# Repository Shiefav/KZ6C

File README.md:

# KZ6C — six-button CH552 USB macropad (prototype B02.1)

A 64 × 64 mm two-layer PCB with three MX-style switches and three 6 × 6 mm tactile switches, USB-C, CH552G and seven individually addressable RGB LEDs. This is an experimental design: it has not yet been validated on a physical prototype and is not a production-ready release.

- `hardware/`: editable KiCad 10 schematic, PCB, project and project-local libraries.
- `firmware/`: CH552 firmware source, vendored dependencies, attribution and firmware license. Requires SDCC; run `make all` inside that directory to build. No flashing is performed by this command.
- `case/`: preliminary sandwich-case OpenSCAD, DXF outlines and an approximate assembly generator. Switch dimensions, fasteners, LED illumination and actual USB clearance require physical fit checks.

## Prototype checks

Check the tactile switch footprint, pad dimensions, height and paired contacts against actual purchased parts. Check component orientation including the SK6812-EC20 LEDs, and the BOM/CPL in the assembly provider's viewer. Measure the current in full brightness and USB suspend, inrush when the LEDs switch on, USB startup and wake. Test key combinations, flashing recovery and fit of switches, case and USB cable on real hardware.

The development firmware currently reports FEED:4B16 as a temporary test identity. This is not a permanent assigned identifier; obtain an appropriate VID/PID before product release. A successful KiCad DRC/ERC does not prove electrical, USB or mechanical compliance.

## Attribution and licensing

The firmware is based on PadKit and the CH552 USB/NeoPixel stack by Stefan Wagner. Attribution, modifications and the CC BY-SA 3.0 firmware license are in `firmware/ATTRIBUTION.md` and `firmware/LICENSE`. Original hardware and case are CC BY-SA 4.0. The adapted KiCad USB-C footprint carries the KiCad library exception. See the root LICENSE and hardware/ATTRIBUTION.md. Firmware is CC BY-SA 3.0; retain its upstream notices.

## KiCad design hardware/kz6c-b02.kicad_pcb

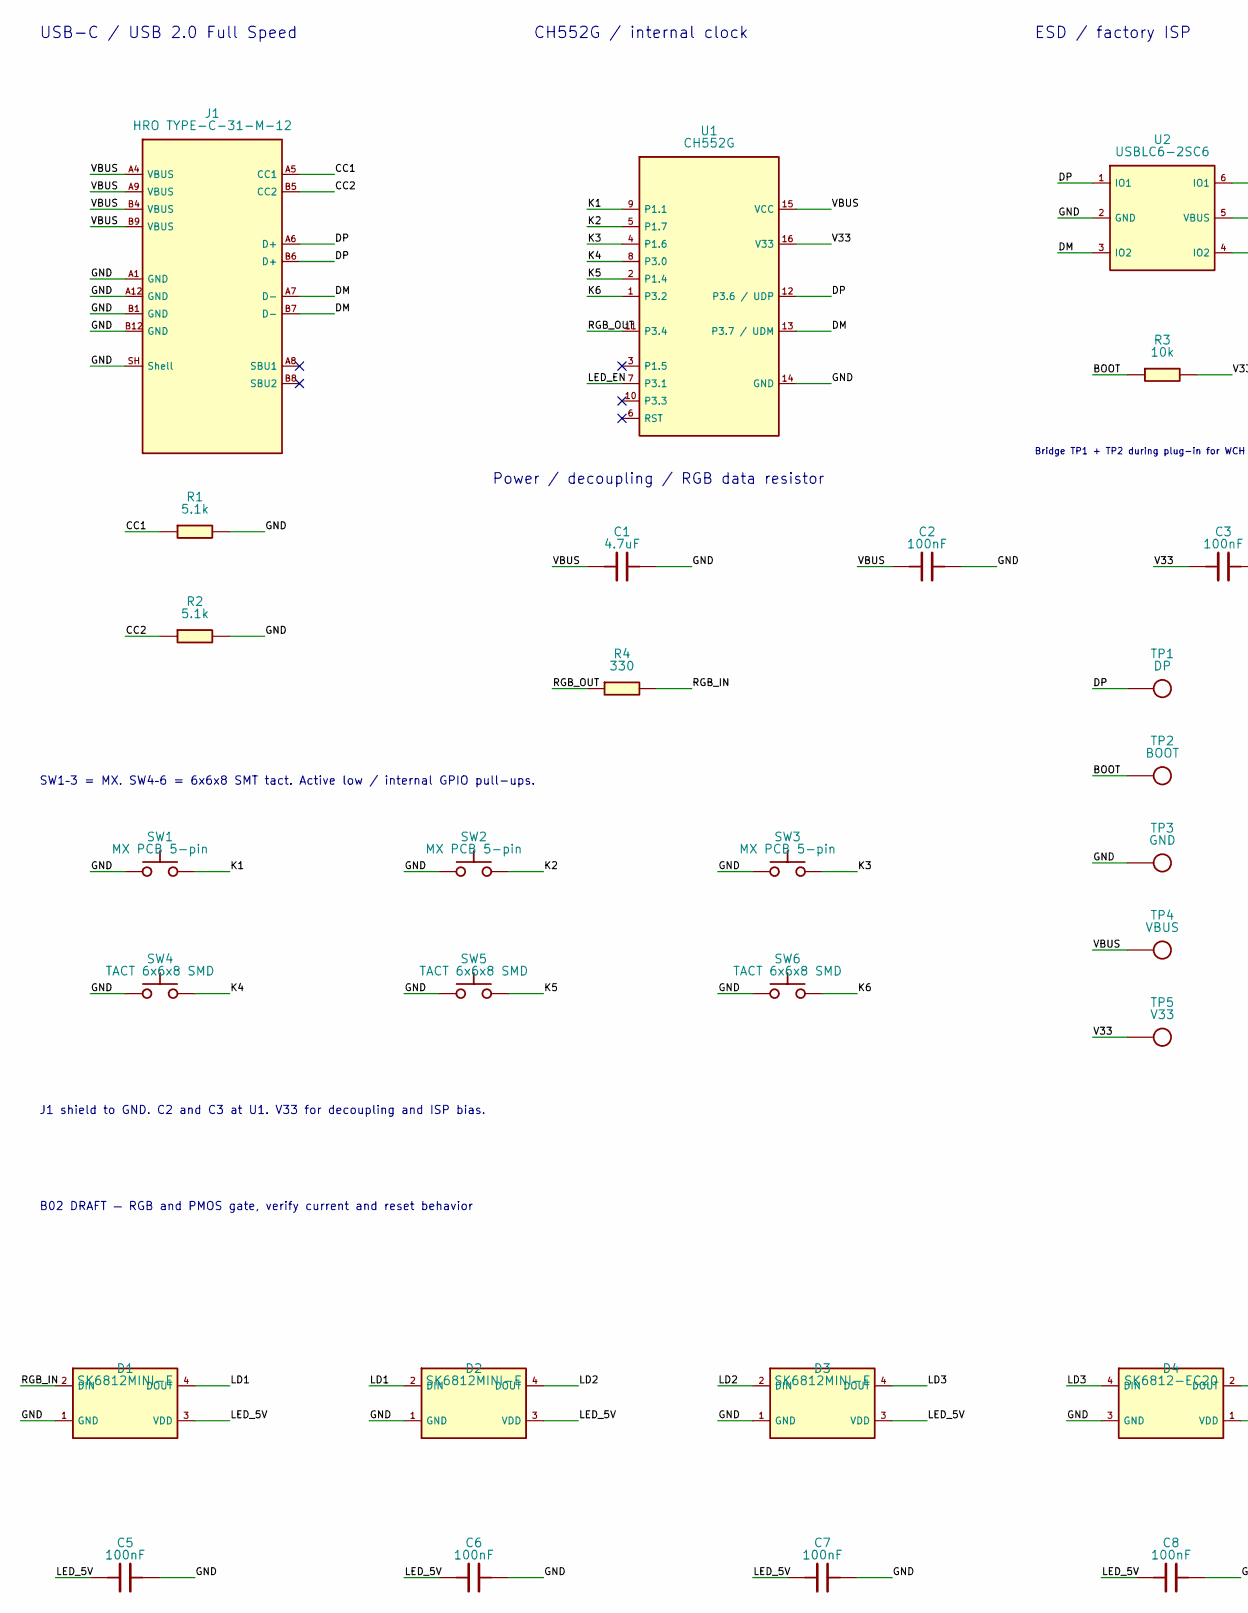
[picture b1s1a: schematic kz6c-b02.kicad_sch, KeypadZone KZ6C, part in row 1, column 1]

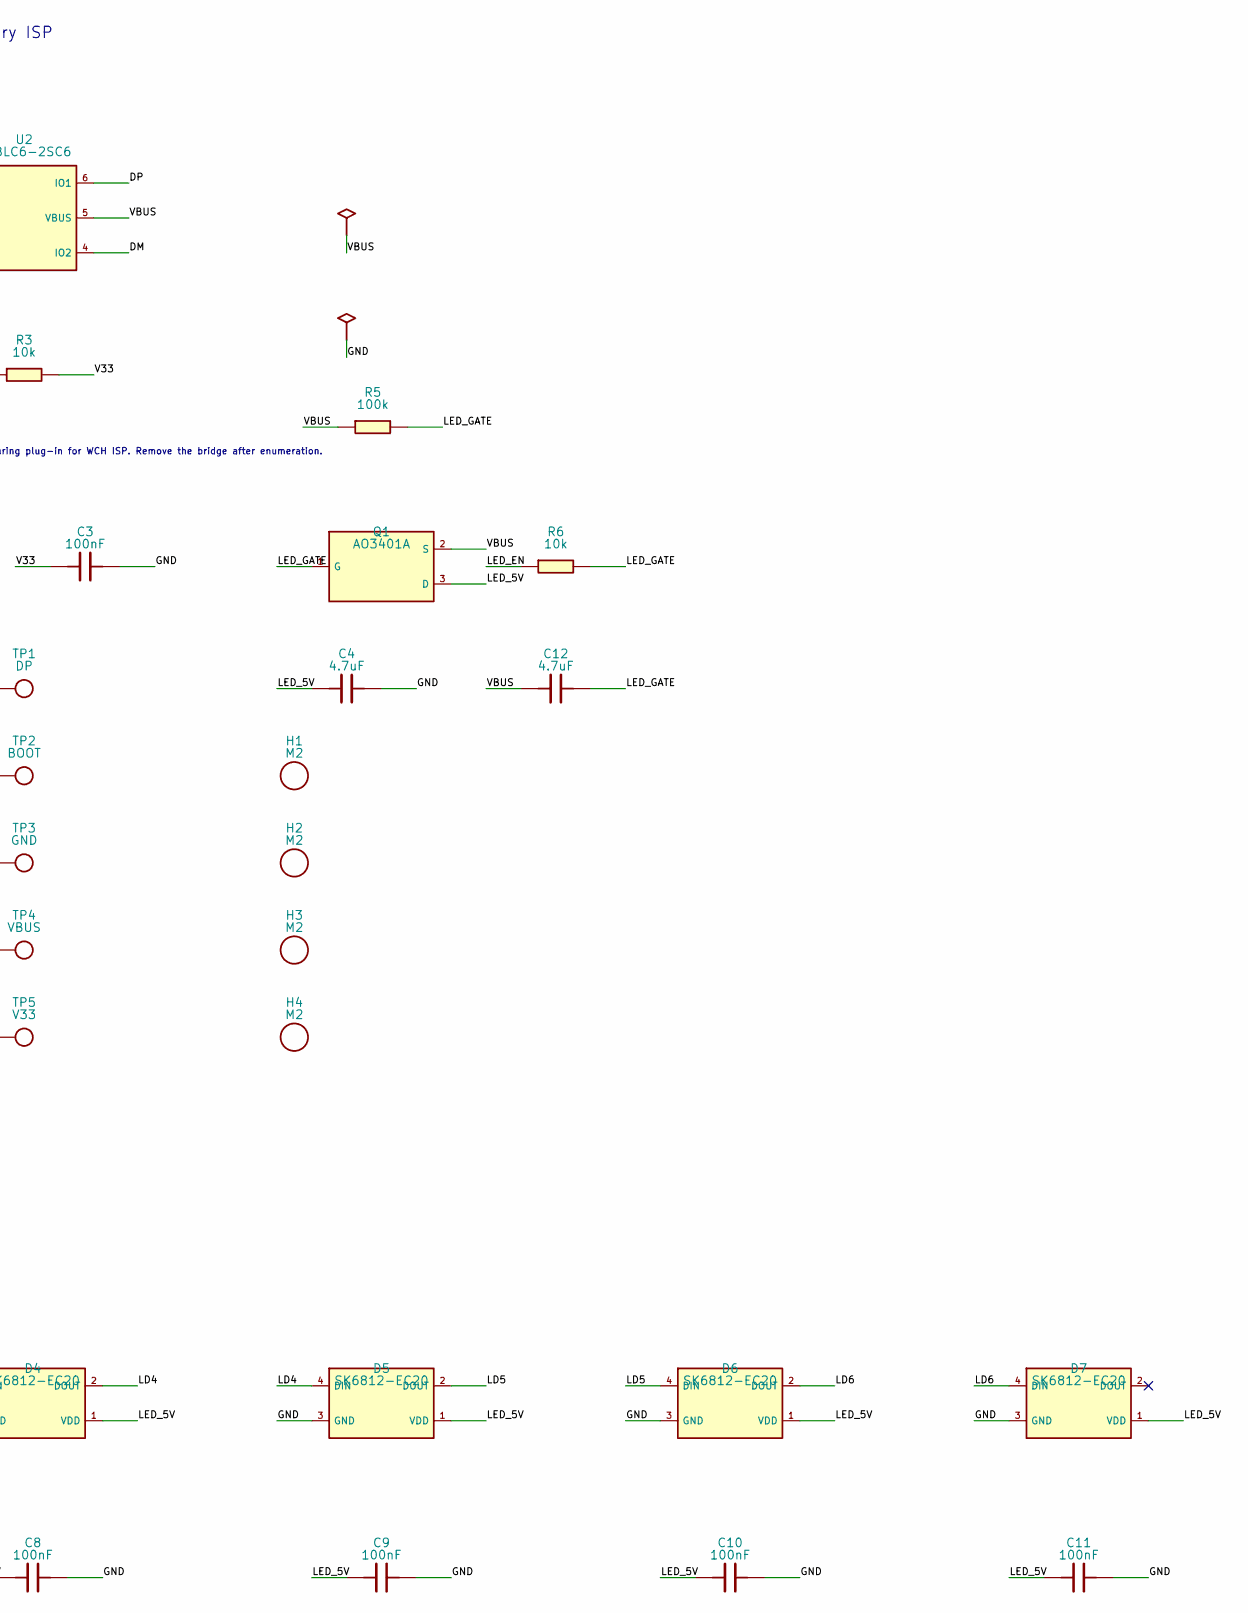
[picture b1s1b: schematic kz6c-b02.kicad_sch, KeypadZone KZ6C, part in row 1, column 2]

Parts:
C1, C4, C12: 4.7uF; C_0805_2012Metric; LCSC Part # C1779
C2, C3, C5, C6, C7, C8, C9, C10, C11: 100nF; C_0805_2012Metric; LCSC Part # C49678
D1, D2, D3: SK6812MINI-E; LED_SK6812MINI-E_3.2x2.8mm_P1.5mm_ReverseMount; LCSC Part # C5149201
D4, D5, D6, D7: SK6812-EC20; LED_SK6812-EC20_2.0x2.0mm; LCSC Part # C2909058
H1, H2, H3, H4: M2; MountingHole_2.2mm_M2
J1: HRO TYPE-C-31-M-12; USB_C_HRO_TYPE-C-31-M-12; LCSC Part # C165948
Q1: AO3401A; SOT-23; LCSC Part # C15127
R1, R2: 5.1k; R_0805_2012Metric; LCSC Part # C27834
R3, R6: 10k; R_0805_2012Metric; LCSC Part # C17414
R4: 330; R_0805_2012Metric; LCSC Part # C17630
R5: 100k; R_0805_2012Metric; LCSC Part # C149504
SW1, SW2, SW3: MX PCB 5-pin; SW_Cherry_MX_1.00u_PCB
SW4, SW5, SW6: TACT 6x6x8 SMD; SW_TACT_6x6_SMD_8.5x4.5
TP1: DP; TestPoint_Pad_D1.0mm
TP2: BOOT; TestPoint_Pad_D1.0mm
TP3: GND; TestPoint_Pad_D1.0mm
TP4: VBUS; TestPoint_Pad_D1.0mm
TP5: V33; TestPoint_Pad_D1.0mm
U1: CH552G; SOIC-16_3.9x9.9mm_P1.27mm; LCSC Part # C111292
U2: USBLC6-2SC6; SOT-23-6; LCSC Part # C7519

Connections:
/BOOT: R3.1, TP2.1
/CC1: J1.A5 (CC1), R1.1
/CC2: J1.B5 (CC2), R2.1
/DM: J1.A7 (D-), J1.B7 (D-), U1.13 (P3.7 / UDM), U2.3 (IO2), U2.4 (IO2)
/DP: J1.A6 (D+), J1.B6 (D+), TP1.1, U1.12 (P3.6 / UDP), U2.1 (IO1), U2.6 (IO1)
/GND: C1.2, C2.2, C3.2, C4.2, C5.2, C6.2, C7.2, C8.2, C9.2, C10.2, C11.2, D1.1 (GND), D2.1 (GND), D3.1 (GND), D4.3 (GND), D5.3 (GND), D6.3 (GND), D7.3 (GND), J1.A1 (GND), J1.A12 (GND), J1.B1 (GND), J1.B12 (GND), J1.SH (Shell), R1.2, R2.2, SW1.1, SW2.1, SW3.1, SW4.1, SW5.1, SW6.1, TP3.1, U1.14 (GND), U2.2 (GND)
/K1: SW1.2, U1.9 (P1.1)
/K2: SW2.2, U1.5 (P1.7)
/K3: SW3.2, U1.4 (P1.6)
/K4: SW4.2, U1.8 (P3.0)
/K5: SW5.2, U1.2 (P1.4)
/K6: SW6.2, U1.1 (P3.2)
/LD1: D1.4 (DOUT), D2.2 (DIN)
/LD2: D2.4 (DOUT), D3.2 (DIN)
/LD3: D3.4 (DOUT), D4.4 (DIN)
/LD4: D4.2 (DOUT), D5.4 (DIN)
/LD5: D5.2 (DOUT), D6.4 (DIN)
/LD6: D6.2 (DOUT), D7.4 (DIN)
/LED_5V: C4.1, C5.1, C6.1, C7.1, C8.1, C9.1, C10.1, C11.1, D1.3 (VDD), D2.3 (VDD), D3.3 (VDD), D4.1 (VDD), D5.1 (VDD), D6.1 (VDD), D7.1 (VDD), Q1.3 (D)
/LED_EN: R6.1, U1.7 (P3.1)
/LED_GATE: C12.2, Q1.1 (G), R5.2, R6.2
/RGB_IN: D1.2 (DIN), R4.2
/RGB_OUT: R4.1, U1.11 (P3.4)
/V33: C3.1, R3.2, TP5.1, U1.16 (V33)
/VBUS: C1.1, C2.1, C12.1, J1.A4 (VBUS), J1.A9 (VBUS), J1.B4 (VBUS), J1.B9 (VBUS), Q1.2 (S), R5.1, TP4.1, U1.15 (VCC), U2.5 (VBUS)

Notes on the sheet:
USB-C / USB 2.0 Full Speed
CH552G / internal clock
ESD / factory ISP
Bridge TP1 + TP2 during plug-in for WCH ISP. Remove the bridge after enumeration.
Power / decoupling / RGB data resistor
SW1–3 = MX. SW4–6 = 6x6x8 SMT tact. Active low / internal GPIO pull-ups.
J1 shield to GND. C2 and C3 at U1. V33 for decoupling and ISP bias.
B02 DRAFT — RGB and PMOS gate, verify current and reset behavior

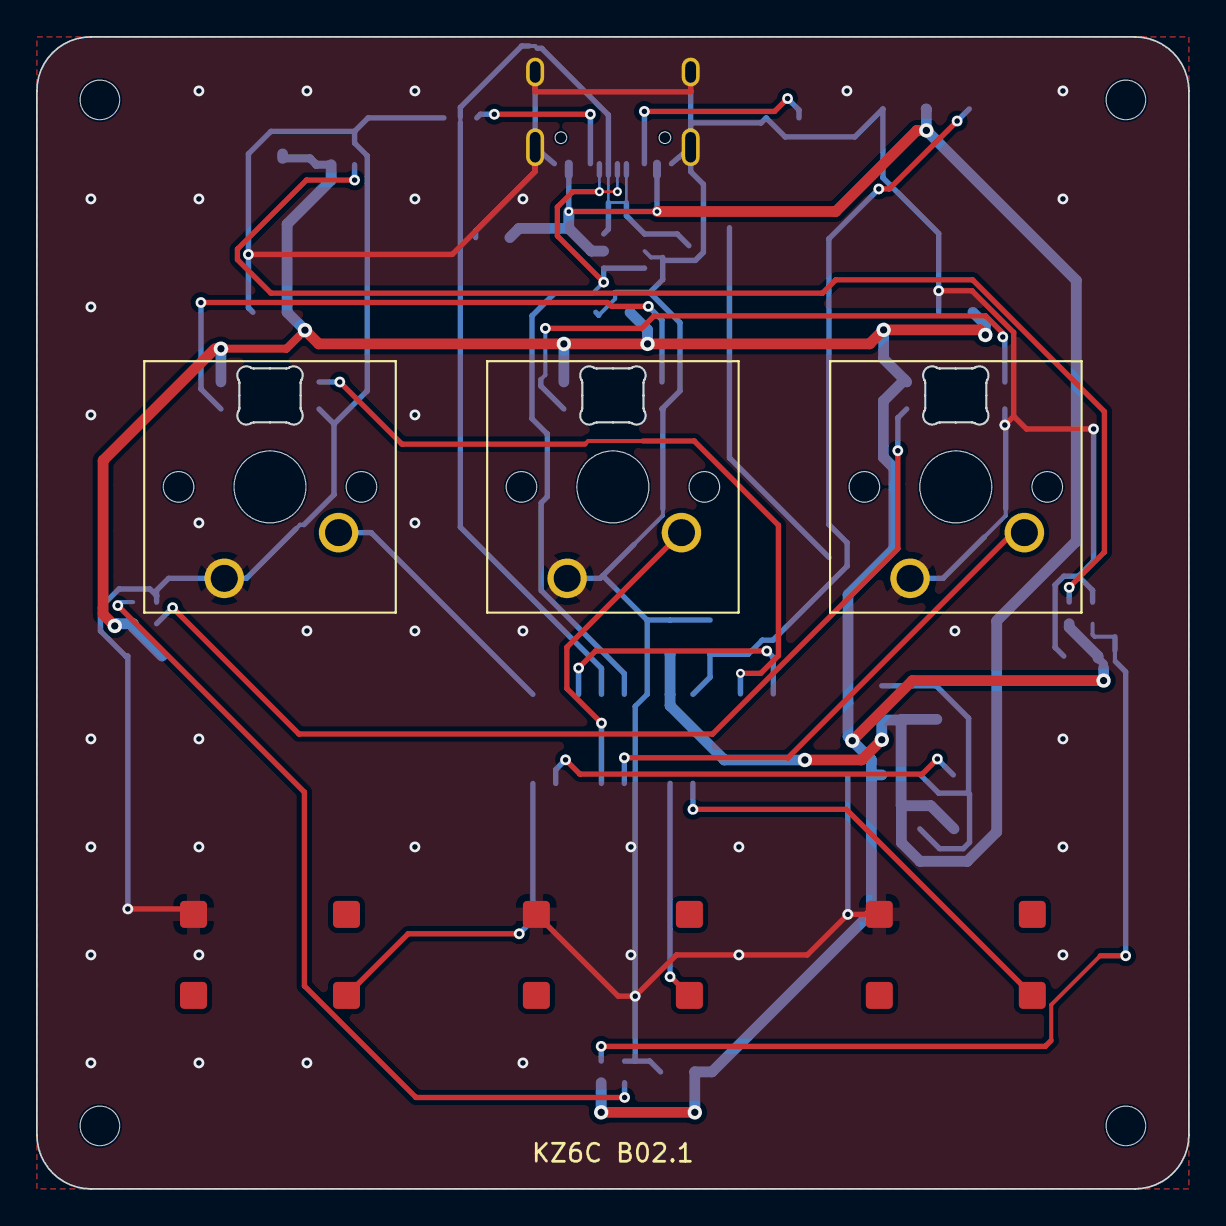
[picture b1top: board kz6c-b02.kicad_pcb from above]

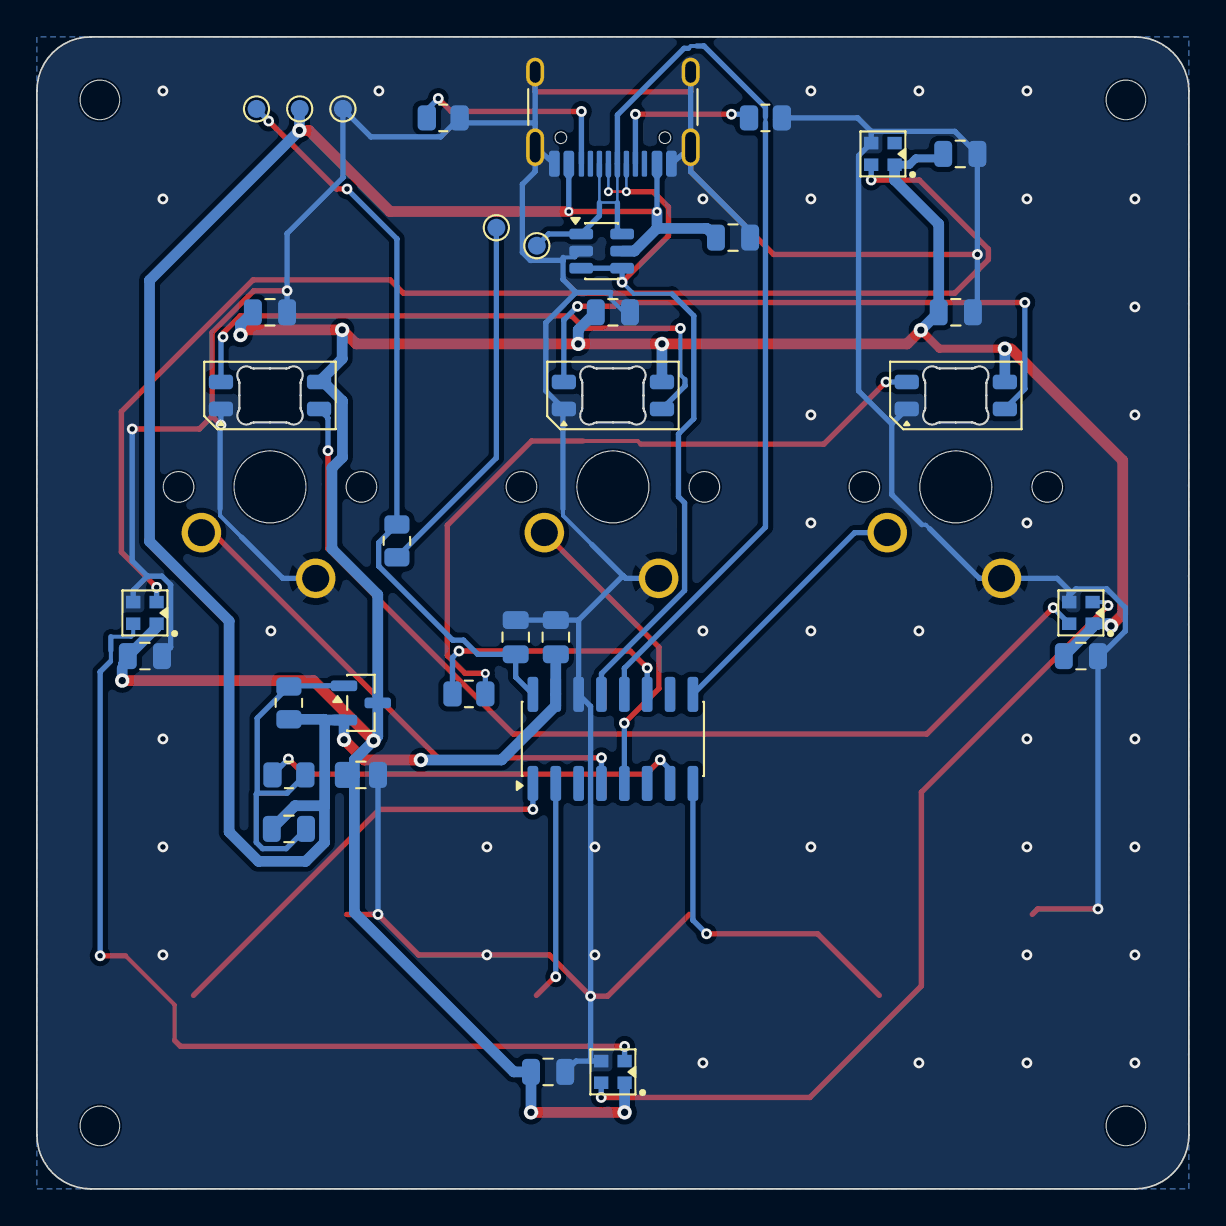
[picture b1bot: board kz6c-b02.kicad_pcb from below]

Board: 2 copper layers, 64.0 x 64.0 mm, 44 parts (34 on the bottom side), 25 nets.
